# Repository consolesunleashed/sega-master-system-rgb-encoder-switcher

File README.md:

Working on designs to release for free can be both time consuming and expensive. If you like what I do, a small donation will go a long way in helping me continue to serve the modding community as best as I can, with many more free and original guides, designs, and ideas to come.

# Sega Master System RGB Encoder Switcher

The Master System RGB Encoder Switcher is designed to allow a Master System to be modded for true PAL and true NTSC. It provides a way to switch the RGB Encoder, usually a CXA1145P or MB3514, between PAL and NTSC operating modes via Pin 7, and route the correct subcarrier clock to Pin 6.

## How?

It's very simple.

1 - Re-routing clock signals

It takes the Z80 clock and the PAL subcarrier clock and sends them into a multiplexer. A switchless region mod will switch the multiplexer between these two inputs so only one is output to Pin 6 of the RGB Encoder.

2 - Inverting the region switch signal

The Master System region setting is the opposite of the RGB Encoder region setting.

CXA1145P/MB3514

- Low = PAL
- High = NTSC

The Master System

- Low = 60Hz
- High = 50Hz

Because of this the standard switch output of a Master Sysem region mod can not switch the RGB Encoder to match the region of the console. So the mod inverts the switch signal so it can be sent to Pin 7 of the RGB Encoder.

That's it. Just a multiplexer and an inverter.

## Why?

1 - Because it was never previously possible to have a genuine PAL and a genuine NTSC Master System in one.

2 - Sometimes it's fun to play in composite video and this means there is full compatibility with PAL and NTSC TVs.

3 - It was fun to identify a problem, study the system to try work out a solution, then design a brand new mod kit.

## Requirements

1 - A way to generate a PAL and NTSC master clock such as a Dual Frequency Oscillator.

2 - A switchless region mod or a physical region switch to switch the RGB Encoder Switcher, VDP Pin 57, and DFO at the same time.

## Compatibility

- Model 2 / PAL / 171-6395A
- Model 2 / PAL / 171-5922A

Others need to be tested but in theory it should work with any Master System that has a Z80 CPU, a SEGA 315-5237 IO IC, and a 4 pin master clock oscillator.

## Mod Kit Variations

There are two versions of this mod kit.

1 - A quick solder board (QSB) PCB version that solders beneath the Z80 CPU.

2 - A standard miniature PCB version which will need fully wiring. This version is intended for experimentation and checking console revision compatibility.

## Version History

Quick Solder Board
- RGB Encoder Switcher v1.0 - 24/03/2023
- RGB Encoder Switcher v1.1 - 02/04/2023
- RGB Encoder Switcher v1.2 - 06/05/2023

Standard
- RGB Encoder Switcher v1.0 - 24/03/2023
- RGB Encoder Switcher v1.1 - 06/05/2023

## Manufacturing

- 1mm or 0.8mm PCB thickness are both fine.
- Castellated vias are optional. There is only three cut vias and the board is thin which generally doesn't result in torn up copper platting. A little cleanup is usually necessary to remove debris from the half vias.

## License

If you use this in any way, shape or form, you must include a link back to this repository and mention me by name on any sales pages and social media posts. Not only will this help me to keep designing mod kits and offering them to the community, but it is basic common courtesy as well. Don't be a douchebag. :)

Also this 'GNU GENERAL PUBLIC LICENSE Version 2, June 1991'.

## Donate

Working on designs to release for free can be both time consuming and expensive. If you like what I do, a small donation will go a long way in helping me continue to serve the modding community as best as I can, with many more free and original guides, designs, and ideas to come.

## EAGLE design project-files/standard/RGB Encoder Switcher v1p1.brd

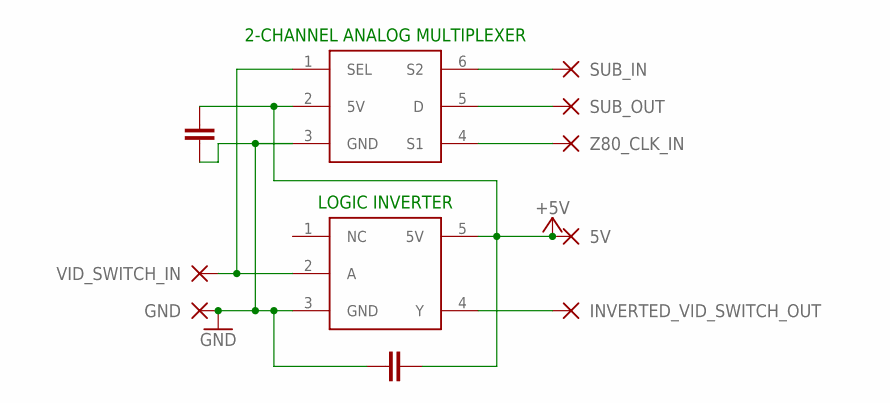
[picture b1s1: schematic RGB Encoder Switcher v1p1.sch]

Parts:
5V: WIREPADCIRCLE-1,5X1,5; CIRCLE-1,5X1,5
C1, C2: 0.1uF; C0603
GND: WIREPADCIRCLE-1,5X1,5; CIRCLE-1,5X1,5
INVERTED_VID_SWITCH_OUT: WIREPADCIRCLE-1,5X1,5; CIRCLE-1,5X1,5
INVERTER: 74AHCT1G04DBVRE4; SOT95P280X110-5N
MULTIPLEXER: TMUX1219DBVR; SOT95P280X110-6N
SUB_IN: WIREPADCIRCLE-1,5X1,5; CIRCLE-1,5X1,5
SUB_OUT: WIREPADCIRCLE-1,5X1,5; CIRCLE-1,5X1,5
VID_SWITCH_IN: WIREPADCIRCLE-1,5X1,5; CIRCLE-1,5X1,5
Z80_CLK_IN: WIREPADCIRCLE-1,5X1,5; CIRCLE-1,5X1,5

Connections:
+5V: 5V.1, C1.1, C2.2, INVERTER.5 (5V), MULTIPLEXER.2 (5V)
GND: C1.2, C2.1, GND.1, INVERTER.3 (GND), MULTIPLEXER.3 (GND)
INVERTED_VID_SWITCH_OUT: INVERTED_VID_SWITCH_OUT.1, INVERTER.4 (Y)
SUB_IN: MULTIPLEXER.6 (S2), SUB_IN.1
SUB_OUT: MULTIPLEXER.5 (D), SUB_OUT.1
VID_SWITCH_IN: INVERTER.2 (A), MULTIPLEXER.1 (SEL), VID_SWITCH_IN.1
Z80_CLK_IN: MULTIPLEXER.4 (S1), Z80_CLK_IN.1

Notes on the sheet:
LOGIC INVERTER
2-CHANNEL ANALOG MULTIPLEXER

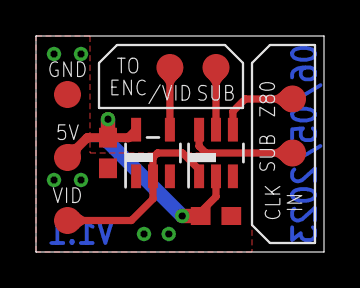
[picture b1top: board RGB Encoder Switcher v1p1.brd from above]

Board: 2 copper layers, 16.0 x 12.0 mm, 11 parts (0 on the bottom side), 7 nets.

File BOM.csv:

Part,MPN,Value,Case/Size,Amount
Multiplexor,TMUX1219DBVR,,SOT-23-6,1
Inverter,4AHCT1G04DBVRE4,,SOT-23-5,1
Capacitor,CL10B104KA8NNNC,0.1uF / 25V,0603,2
